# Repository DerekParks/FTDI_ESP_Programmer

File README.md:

# A FTDI Breakout with auto reset

## Motivation

Around 2008-ish Sparkfun started selling their [FTDI basic breakout](https://www.sparkfun.com/products/retired/9115). 
These were great! And really helped me move beyond having a full Arduino Uno inside of every project.

Fast forward to today. ESP's are king! But we are in a similar situation where [most dev boards](https://components101.com/development-boards/nodemcu-esp8266-pinout-features-and-datasheet) include a built in USB-to-TTL chip.
At least now, we are using FTDI clones that are cheaper. But I still don't want to include extra hardware just for programming in every project! 

For years I have used the [3.3v version of Sparkfun's FTDI breakout](https://www.sparkfun.com/products/9873) for programming ESP's. 
And for an equal amount of years, I've been annoyed that auto-reset doesn't work like on the all-in-one dev boards.

I will freely admit that support for OTA updates has made this less of an annoyance. But when I am working out bugs, I find iterating with a physical programmer faster.

So at some point during the pandemic, I setout to figure out how [the auto-reset feature on ESP's works](https://hallard.me/esp8266-autoreset/) and to make my own FTDI programmer.

## The Programmer

("V1 where I forgot to add current limiting resistors to the status LED's, D'oh!")

There are also physical tactical flash and reset buttons in case for some reason my amazing auto-reset circuit fails. 

## New standard pinout?

Do I even need to link the standards xkcd[?](https://xkcd.com/927/) Yes, I am proposing a new standard pinout.

| Old Pinouts | My Pinout   |
| ----------- | ----------- |
| DTR         | RST         |
| RX          | RX          |
| TX          | TX          |
| VCC         | VCC         |
| CTS         | GPIO0       |
| GND         | GND         |

As you can see I've replaced DTR and CTS with RST and GPIO0, respectively. This board does have the original FTDI standard pins broken out, just-in-case, but so far I haven't ever had cause to use them.

## 3.3 or 5?

There is a solder jumper on the board to switch between 3.3v and 5v. It is set to 3.3v by default.

## C6 & C7

The decoupling, C6 & C7 should be removed if using an ESP01 and I2C.

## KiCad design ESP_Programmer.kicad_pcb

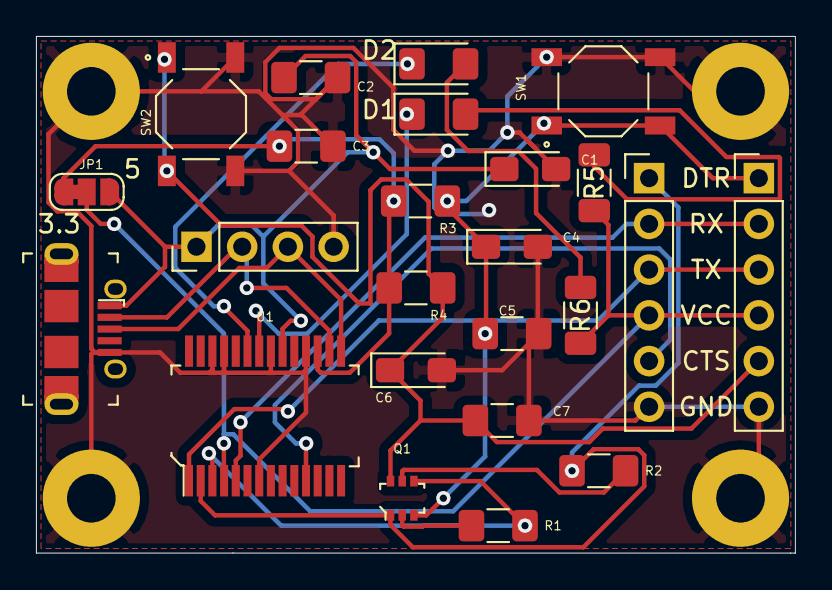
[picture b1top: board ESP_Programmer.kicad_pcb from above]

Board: 2 copper layers, 42.2 x 28.7 mm, 28 parts (0 on the bottom side), 19 nets.

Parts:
C1, C4, C6: 10uF; CP_EIA-3216-18_Kemet-A_Pad1.58x1.35mm_HandSolder
C2, C3, C5, C7: 0.1uF; C_1206_3216Metric_Pad1.42x1.75mm_HandSolder
D1, D2: LED; LED_1206_3216Metric_Pad1.42x1.75mm_HandSolder
H1, H2, H3, H4: MountingHole_Pad; MountingHole_2.7mm_M2.5_Pad
J1: USB_B_Micro; USB_Micro_AB_Female_0475890001
J2: Conn_01x04_Female; PinHeader_1x04_P2.54mm_Vertical
J3: FTDI_Header
J4: ESP_PROG; PinHeader_1x06_P2.54mm_Vertical
JP1: SolderJumper_3_Bridged12; SolderJumper-3_P1.3mm_Bridged12_RoundedPad1.0x1.5mm_NumberL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
Q1: MBT3904DW1T1G; SOT-363
R1, R2: 10K; R_1206_3216Metric_Pad1.42x1.75mm_HandSolder
R3, R4: 10k; R_1206_3216Metric_Pad1.42x1.75mm_HandSolder
R5, R6: 270; R_1206_3216Metric_Pad1.30x1.75mm_HandSolder
SW1, SW2: SW_SPST_SM_DP; E-Switch-TL3342F160QG-0
U1: FT232RL-REEL; SSOP-28_W5.30mm

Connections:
+3V3: C3.1, JP1.1, R3.1, R4.1, U1.17
+5V: C1.1, C2.2, J1.1, J2.1, JP1.3, U1.20
CTS: J3.5, U1.11
D+: J1.3, J2.3, U1.15
D-: J1.2, J2.2, U1.16
DTR: J3.1, Q1.1, R2.2, U1.2
GND: C1.2, C2.1, C3.2, C4.2, C5.2, C6.2, C7.2, H1.1, H2.1, H3.1, H4.1, J1.5, J2.4, J3.6, J4.6, SW1.3, SW1.4, SW2.3, SW2.4, U1.7, U1.18, U1.21, U1.25, U1.26
GPIO0: C6.1, C7.1, J4.5, Q1.6, R4.2, SW2.1, SW2.2
unnamed: D1.2, R5.2
unnamed: D2.2, R6.2
unnamed: Q1.2, R1.2
unnamed: Q1.5, R2.1
PWR_IO: J3.4, J4.4, JP1.2, R5.1, R6.1, U1.4
RST: C4.1, C5.1, J4.1, Q1.3, R3.2, SW1.1, SW1.2
RTS: Q1.4, R1.1, U1.3
RXI: J3.2, J4.2, U1.5
RXLED: D1.1, U1.22
TXLED: D2.1, U1.23
TXO: J3.3, J4.3, U1.1

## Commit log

2021-05-14 Inital commit
2021-08-21 Remove ignored files
2021-08-21 Added readme
2021-08-23 Add images
2021-08-23 Fix image paths
2021-08-23 Readme fixes
2022-05-11 V2 led's and notes about C6 & C7
2022-05-11 readmed updates
